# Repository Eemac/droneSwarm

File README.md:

# droneSwarm
Code and build log for a PCB quadcopter swarm.

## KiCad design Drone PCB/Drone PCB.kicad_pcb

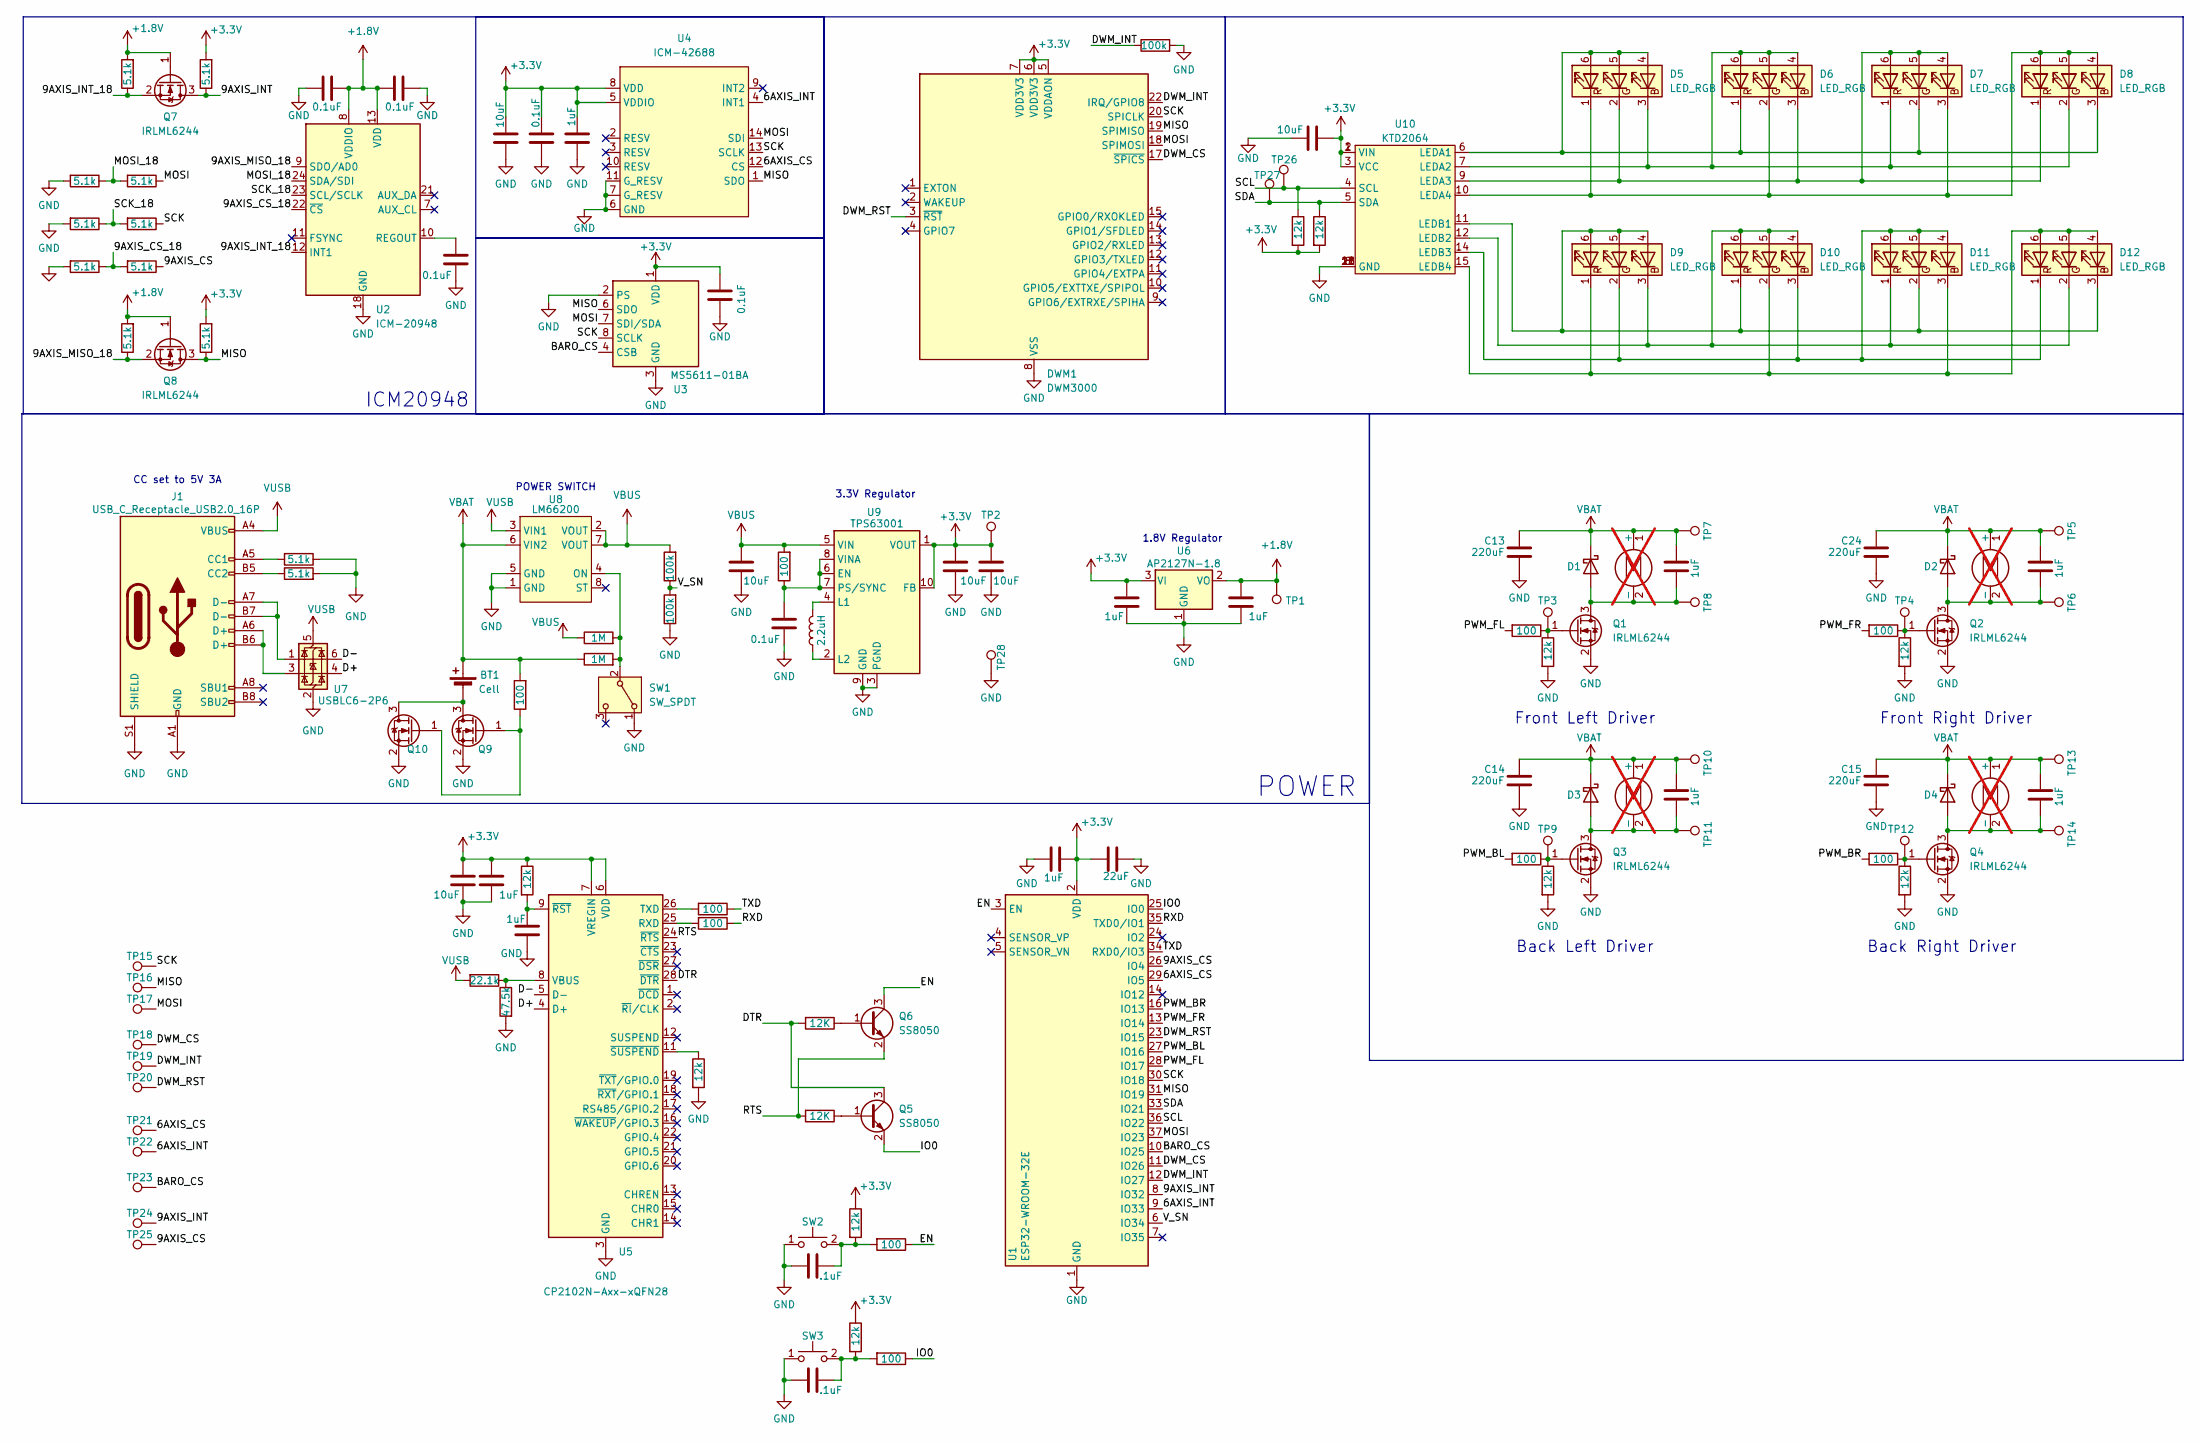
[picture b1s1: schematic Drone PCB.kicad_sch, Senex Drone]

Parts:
BT1: Cell; Battery Holder
C3, C8, C9, C10, C20, C31: 10uF; C_0603; MPN LMK107BBJ106KALT
C4, C5, C6, C22, C23, C26, C27, C28, C29, C30: 1uF; C_0603; MPN LMK107BBJ106KALT
C7, C16, C17, C18, C19, C21: 0.1uF; C_0603; MPN LMK107BBJ106KALT
C11, C12: .1uF; C_0603_1608Metric
C13, C14, C15, C24: 220uF; C_1206_3216Metric
C25: 22uF; C_1206_3216Metric
D1, D2, D3, D4: D_Schottky; D_SOD-123F
D5, D6, D7, D8, D9, D10, D11, D12: LED_RGB; LED_RGB_5050-6
DWM1: DWM3000; DWM1000
J1: USB_C_Receptacle_USB2.0_16P; USB_C_Receptacle_GCT_USB4105-xx-A_16P_TopMnt_Horizontal
L1: 2.2uH; L_1008_2520Metric
M1, M2, M3, M4: Motor_DC; not fitted
Q1, Q2, Q3, Q4, Q7, Q8, Q9, Q10: IRLML6244; SOT-23
Q5, Q6: SS8050; SOT-23
R1, R2, R18, R19, R20, R21, R22, R23, R24, R25, R26, R27: 5.1k; R_0603_1608Metric
R3, R4: 1M; R_0603_1608Metric
R5, R6: 12K; R_0603_1608Metric
R7, R11, R12, R14, R30, R32, R33, R35, R40, R41: 100; R_0603_1608Metric
R9, R13, R17, R29, R31, R34, R36, R38, R39, R42: 12k; R_0603_1608Metric
R15, R43, R44: 100k; R_0603_1608Metric
R28: 22.1k; R_0603_1608Metric
R37: 47.5k; R_0603_1608Metric
SW1: SW_SPDT; SW_SPDT_CK_JS102011SAQN
SW2, SW3: SW_Push_SPST_NO; SW_B3U-1000P_4.2x1.7mm; MPN B3U-1000P
TP1, TP2, TP15, TP16, TP17, TP18, TP19, TP20, TP21, TP22, TP23, TP24, TP25, TP26, TP27, TP28: TestPoint; TestPoint_Pad_D1mm
TP3, TP4, TP9, TP12: TestPoint; TestPoint_Pad_D1.0mm
TP5, TP6, TP7, TP8, TP10, TP11, TP13, TP14: TestPoint; TestPoint_Pad_3.0x3.0mm
U1: ESP32-WROOM-32E; ESP32-WROOM-32D
U2: ICM-20948; InvenSense_QFN-24_3x3mm_P0.4mm
U3: MS5611-01BA; LGA-8_3x5mm_P1.25mm
U4: ICM-42688; LGA-14_3x2.5mm_P0.5mm_LayoutBorder3x4y
U5: CP2102N-Axx-xQFN28; QFN-28-1EP_5x5mm_P0.5mm_EP3.35x3.35mm
U6: AP2127N-1.8; SOT-23
U7: USBLC6-2P6; SOT-666
U8: LM66200; SOT-5X3
U9: TPS63001; Texas_DRC0010J_ThermalVias
U10: KTD2064; QFN-20-1EP_3x3mm_P0.4mm_EP1.65x1.65mm

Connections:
+1.8V: C5.1, C17.1, C18.2, Q7.1 (G), Q8.1 (G), R24.2, R26.2, TP1.1, U2.8 (VDDIO), U2.13 (VDD), U6.2 (VO)
+3.3V: C3.1, C4.1, C6.1, C9.1, C10.1, C19.2, C20.1, C21.1, C22.1, C23.2, C25.1, C31.2, DWM1.5 (VDDAON), DWM1.6 (VDD3V3), DWM1.7 (VDD3V3), R9.1, R13.1, R17.1, R25.2, R27.2, R38.2, R39.2, TP2.1, U1.2 (VDD), U3.1 (VDD), U4.5 (VDDIO), U4.8 (VDD), U5.6 (VDD), U5.7 (VREGIN), U6.3 (VI), U9.1 (VOUT), U9.10 (FB), U10.1 (VIN), U10.2 (VIN), U10.3 (VCC)
/6AXIS_CS: TP21.1, U1.29 (IO5), U4.12 (CS)
/6AXIS_INT: TP22.1, U1.9 (IO33), U4.4 (INT1)
/9AXIS_CS: R23.1, TP25.1, U1.26 (IO4)
/9AXIS_CS_18: R22.1, R23.2, U2.22 (~CS)
/9AXIS_INT: Q7.3 (D), R25.1, TP24.1, U1.8 (IO32)
/9AXIS_INT_18: Q7.2 (S), R24.1, U2.12 (INT1)
/9AXIS_MISO_18: Q8.2 (S), R26.1, U2.9 (SDO/AD0)
/BARO_CS: TP23.1, U1.10 (IO25), U3.4 (CSB), U3.5 (CSB)
/D+: U5.4 (D+), U7.4 (I/O2)
/D-: U5.5 (D-), U7.6 (I/O1)
/DTR: Q5.3 (C), R5.2, U5.28 (~DTR)
/DWM_CS: DWM1.17 (~SPICS), TP18.1, U1.11 (IO26)
/DWM_INT: DWM1.22 (IRQ/GPIO8), R15.1, TP19.1, U1.12 (IO27)
/DWM_RST: DWM1.3 (~RST), TP20.1, U1.23 (IO15)
/EN: Q6.3 (C), R40.1, U1.3 (EN)
/IO0: Q5.2 (E), R41.1, U1.25 (IO0)
/MISO: DWM1.19 (SPIMISO), Q8.3 (D), R27.1, TP16.1, U1.31 (IO19), U3.6 (SDO), U4.1 (SDO)
/MOSI: DWM1.18 (SPIMOSI), R19.1, TP17.1, U1.37 (IO23), U3.7 (SDI/SDA), U4.14 (SDI)
/MOSI_18: R18.1, R19.2, U2.24 (SDA/SDI)
/PWM_BL: R32.2, U1.27 (IO16)
/PWM_BR: R35.2, U1.16 (IO13)
/PWM_FL: R33.2, U1.28 (IO17)
/PWM_FR: R30.2, U1.13 (IO14)
/RTS: Q6.2 (E), R6.2, U5.24 (~RTS)
/RXD: R14.1, U1.35 (TXD0/IO1)
/SCK: DWM1.20 (SPICLK), R21.1, TP15.1, U1.30 (IO18), U3.8 (SCLK), U4.13 (SCLK)
/SCK_18: R20.1, R21.2, U2.23 (SCL/SCLK)
/SCL: R38.1, TP26.1, U1.36 (IO22), U10.4 (SCL)
/SDA: R39.1, TP27.1, U1.33 (IO21), U10.5 (SDA)
/TXD: R11.1, U1.34 (RXD0/IO3)
/V_SN: R43.1, R44.2, U1.6 (IO34)
GND: C3.2, C4.2, C5.2, C6.2, C7.2, C8.2, C9.2, C10.2, C11.1, C12.1, C13.1, C14.1, C15.1, C16.2, C17.2, C18.1, C19.1, C20.2, C21.2, C22.2, C23.1, C24.1, C25.2, C26.2, C31.1, DWM1.8 (VSS), DWM1.16 (VSS), DWM1.21 (VSS), DWM1.23 (VSS), DWM1.24 (VSS), J1.A1 (GND), J1.A12 (GND), J1.B1 (GND), J1.B12 (GND), J1.S1 (SHIELD), Q1.2 (S), Q2.2 (S), Q3.2 (S), Q4.2 (S), Q9.2 (S), Q10.2 (S), R1.1, R2.2, R15.2, R18.2, R20.2, R22.2, R29.2, R31.2, R34.2, R36.2, R37.2, R42.2, R44.1, SW1.1 (A), SW2.1, SW3.1, TP28.1, U1.1 (GND), U1.15 (GND), U1.38 (GND), U1.39 (GND), U2.18 (GND), U2.20 (GND), U3.2 (PS), U3.3 (GND), U4.6 (GND), U4.7 (G_RESV), U4.11 (G_RESV), U5.3 (GND), U5.29 (GND), U6.1 (GND), U7.2 (GND), U8.1 (GND), U8.5 (GND), U9.3 (PGND), U9.9 (GND), U9.11 (PGND), U10.8 (GND), U10.13 (GND), U10.18 (GND), U10.21 (GND)
unnamed: BT1.2 (-), Q9.3 (D), Q10.3 (D)
unnamed: C11.2, R13.2, R40.2, SW2.2
unnamed: C12.2, R9.2, R41.2, SW3.2
unnamed: C27.1, D1.2 (A), M1.2 (-), Q1.3 (D), TP8.1
unnamed: C29.1, D2.2 (A), M2.2 (-), Q2.3 (D), TP6.1
unnamed: C28.1, D3.2 (A), M3.2 (-), Q3.3 (D), TP11.1
unnamed: C30.1, D4.2 (A), M4.2 (-), Q4.3 (D), TP14.1
unnamed: D5.4 (BA), D5.5 (GA), D5.6 (RA), D6.1 (RK), D7.2 (GK), D8.3 (BK), U10.6 (LEDA1)
unnamed: D5.3 (BK), D6.4 (BA), D6.5 (GA), D6.6 (RA), D7.1 (RK), D8.2 (GK), U10.7 (LEDA2)
unnamed: D5.2 (GK), D6.3 (BK), D7.4 (BA), D7.5 (GA), D7.6 (RA), D8.1 (RK), U10.9 (LEDA3)
unnamed: D5.1 (RK), D6.2 (GK), D7.3 (BK), D8.4 (BA), D8.5 (GA), D8.6 (RA), U10.10 (LEDA4)
unnamed: D9.3 (BK), D10.4 (BA), D10.5 (GA), D10.6 (RA), D11.1 (RK), D12.2 (GK), U10.12 (LEDB2)
unnamed: D9.2 (GK), D10.3 (BK), D11.4 (BA), D11.5 (GA), D11.6 (RA), D12.1 (RK), U10.14 (LEDB3)
unnamed: D9.1 (RK), D10.2 (GK), D11.3 (BK), D12.4 (BA), D12.5 (GA), D12.6 (RA), U10.15 (LEDB4)
unnamed: D9.4 (BA), D9.5 (GA), D9.6 (RA), D10.1 (RK), D11.2 (GK), D12.3 (BK), U10.11 (LEDB1)
unnamed: J1.A5 (CC1), R1.2
unnamed: J1.B5 (CC2), R2.1
unnamed: J1.A6 (D+), J1.B6 (D+), U7.3 (I/O2)
unnamed: J1.A7 (D-), J1.B7 (D-), U7.1 (I/O1)
unnamed: Q1.1 (G), R29.1, R33.1, TP3.1
unnamed: Q2.1 (G), R30.1, R31.1, TP4.1
unnamed: Q3.1 (G), R32.1, R34.1, TP9.1
unnamed: Q4.1 (G), R35.1, R36.1, TP12.1
unnamed: Q5.1 (B), R6.1
unnamed: Q6.1 (B), R5.1
unnamed: Q9.1 (G), Q10.1 (G), R7.1
unnamed: R3.2, R4.2, SW1.2 (B), U8.4 (ON)
unnamed: C16.1, U2.10 (REGOUT)
unnamed: R14.2, U5.25 (RXD)
unnamed: R11.2, U5.26 (TXD)
unnamed: R28.1, R37.1, U5.8 (VBUS)
unnamed: C26.1, R17.2, U5.9 (~RST)
unnamed: R42.1, U5.11 (~SUSPEND)
unnamed: C7.1, R12.1, U9.6 (EN), U9.7 (PS/SYNC), U9.8 (VINA)
unnamed: L1.2, U9.4 (L1)
unnamed: L1.1, U9.2 (L2)
VBAT: BT1.1 (+), C13.2, C14.2, C15.2, C24.2, C27.2, C28.2, C29.2, C30.2, D1.1 (K), D2.1 (K), D3.1 (K), D4.1 (K), M1.1 (+), M2.1 (+), M3.1 (+), M4.1 (+), R4.1, R7.2, TP5.1, TP7.1, TP10.1, TP13.1, U8.6 (VIN2)
VBUS: C8.1, R3.1, R12.2, R43.2, U8.2 (VOUT), U8.7 (VOUT), U9.5 (VIN)
VUSB: J1.A4 (VBUS), J1.A9 (VBUS), J1.B4 (VBUS), J1.B9 (VBUS), R28.2, U7.5 (VBUS), U8.3 (VIN1)

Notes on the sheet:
Front Left Driver
Back Right Driver
Front Right Driver
ICM20948
Back Left Driver
POWER
POWER SWITCH
3.3V Regulator
1.8V Regulator
CC set to 5V 3A

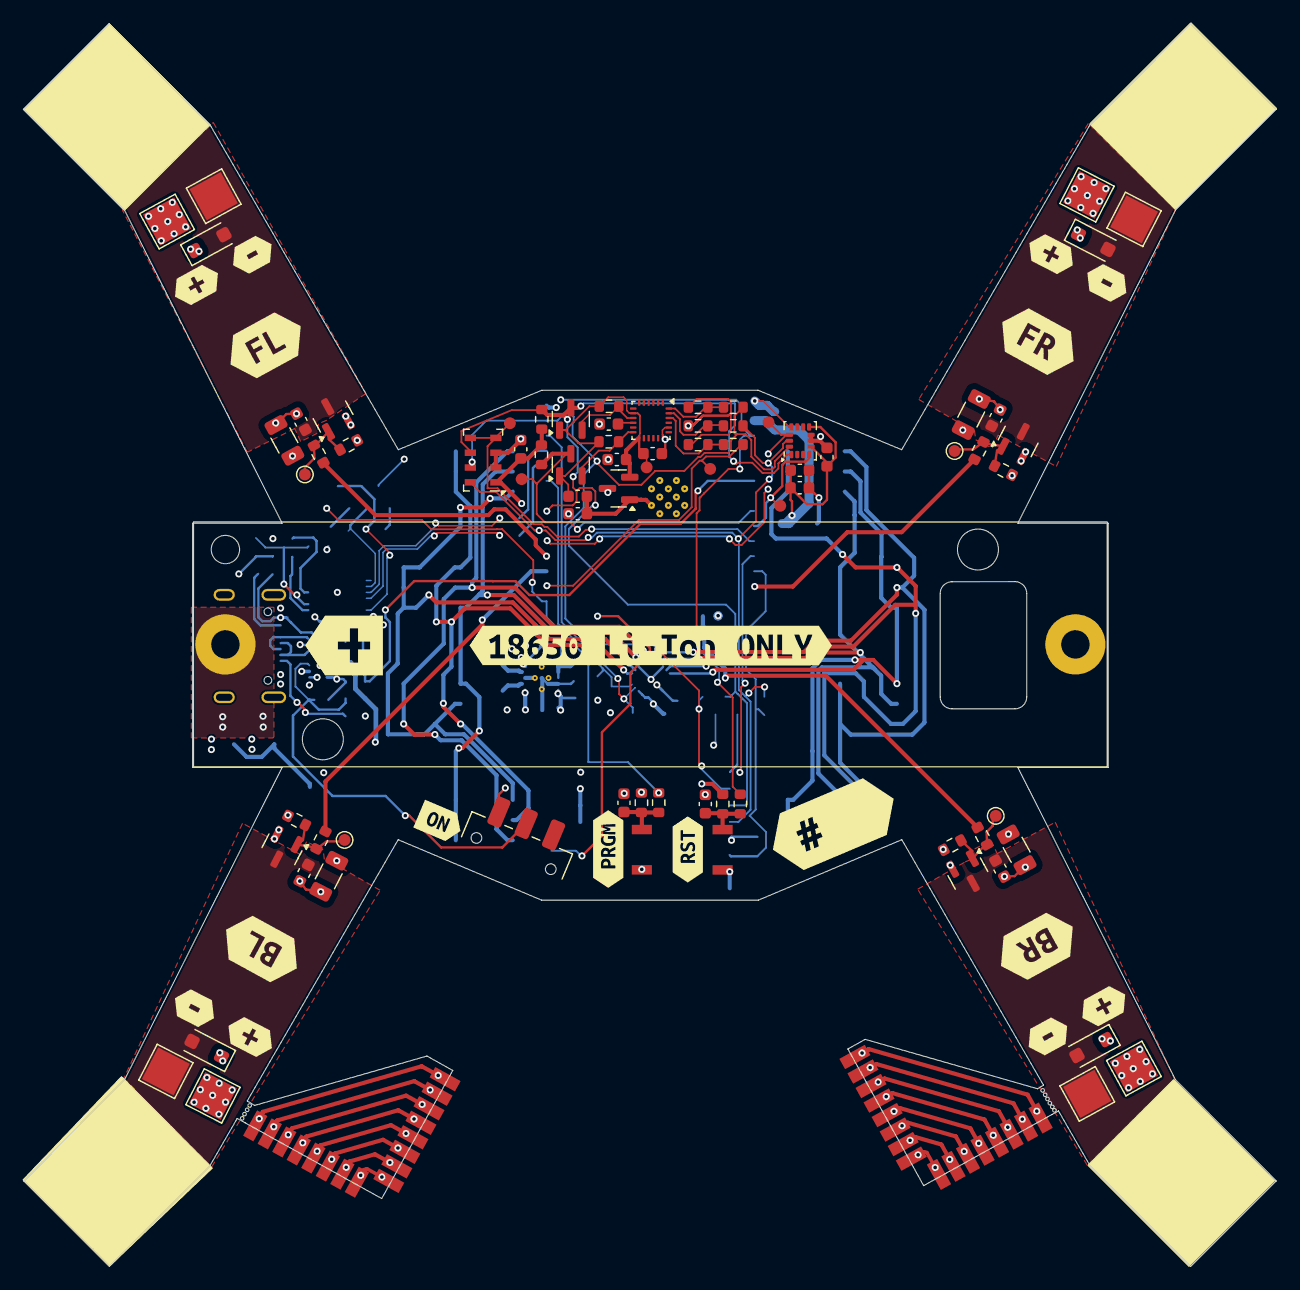
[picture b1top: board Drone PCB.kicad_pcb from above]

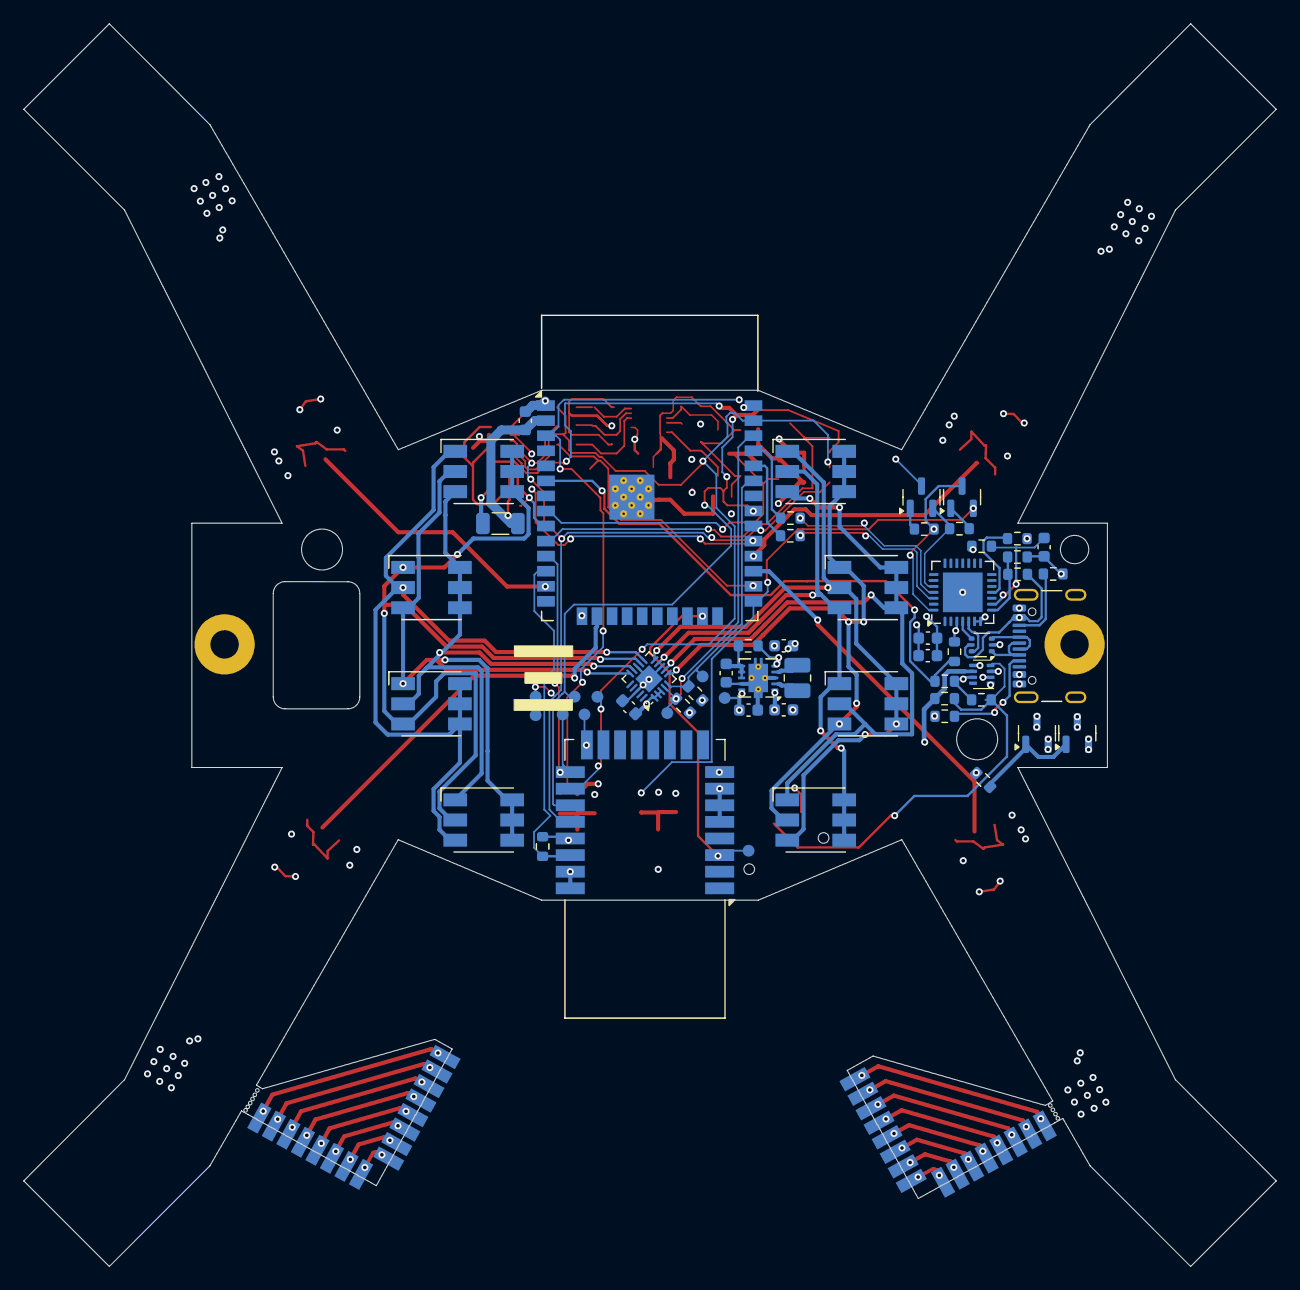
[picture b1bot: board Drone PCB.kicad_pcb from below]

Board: 4 copper layers, 105.6 x 104.8 mm, 155 parts (60 on the bottom side), 73 nets.

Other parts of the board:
kibuzzard-682A6A3A: G***; kibuzzard-682A6A3A
kibuzzard-682A6E86: G***; kibuzzard-682A6E86
kibuzzard-682A6EE1: G***; kibuzzard-682A6EE1
kibuzzard-682A6EFD: G***; kibuzzard-682A6EFD
kibuzzard-682A64DA: G***; kibuzzard-682A64DA
kibuzzard-682A72B2: G***; kibuzzard-682A72B2
kibuzzard-682A717E: G***; kibuzzard-682A717E
kibuzzard-682A719B: G***; kibuzzard-682A719B
kibuzzard-682A6346: G***; kibuzzard-682A6346
kibuzzard-682A6523, kibuzzard-682A6523#2, kibuzzard-682A6523#3, kibuzzard-682A6523#4: G***; kibuzzard-682A6523
kibuzzard-682A6594, kibuzzard-682A6594#2, kibuzzard-682A6594#3, kibuzzard-682A6594#4: G***; kibuzzard-682A6594
kibuzzard-682A7152: G***; kibuzzard-682A7152

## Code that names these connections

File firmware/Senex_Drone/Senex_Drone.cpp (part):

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		pinMode(SIX_AXIS_INT, INPUT);

		//Barometer
		pinMode(BARO_CS, OUTPUT);
		digitalWrite(BARO_CS, HIGH);

		//DWM3000
		pinMode(DWM_CS, OUTPUT);
		digitalWrite(DWM_CS, HIGH);
		pinMode(DWM_INT, INPUT);

		//Propellers
		pinMode(PWM_FR, OUTPUT);
		pinMode(PWM_FL, OUTPUT);
		pinMode(PWM_BR, OUTPUT);
		pinMode(PWM_BL, OUTPUT);
		digitalWrite(PWM_FR, LOW);
		digitalWrite(PWM_FL, LOW);
		digitalWrite(PWM_BR, LOW);
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
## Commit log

2026-03-31 PCB commit
2026-03-31 radiation pattern visualizer + some UWB code
2026-03-31 firmware upload
2026-03-31 images for readme

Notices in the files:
firmware/Senex_Drone/Senex_Drone.cpp:
All Rights Reserved.
